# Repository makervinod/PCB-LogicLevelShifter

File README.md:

# PCB-LogicLevelShifter
## A 6-channel Logic Level Shifter PCB with on-board 3.3V Regulation

Components Required:
1. N-channel SMD(SOT-23) Mosfets x 6
2. 10k SMD(0805) Resistors x 12
3. LM11117-3.3 SMD(SOT-223) Voltage Regulator x 1
4. 0.1uF SMD(0805) Capacitors x 2
5. Red LED SMD(0805) x 1
6. 8-pin Male Headers 2.54mm Pitch x 2

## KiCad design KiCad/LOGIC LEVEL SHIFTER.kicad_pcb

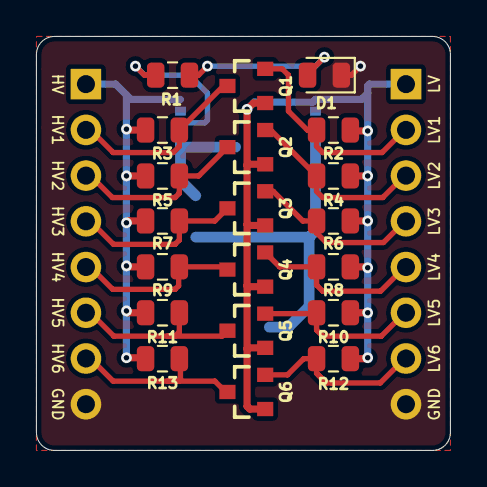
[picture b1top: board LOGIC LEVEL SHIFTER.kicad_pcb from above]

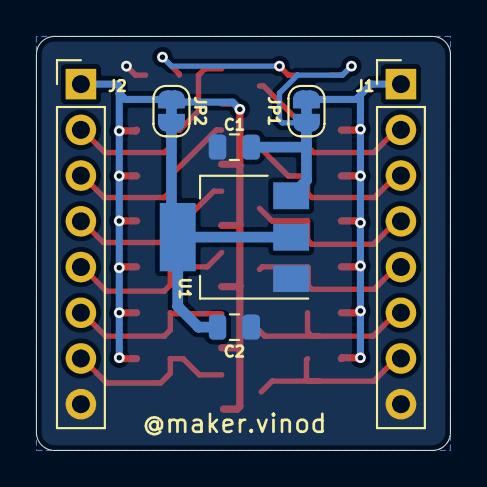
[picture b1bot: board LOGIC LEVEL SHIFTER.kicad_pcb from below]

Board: 2 copper layers, 23.0 x 23.0 mm, 27 parts (7 on the bottom side), 18 nets.

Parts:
C1, C2: 22uF; C_0805_2012Metric
D1: LED; LED_0805_2012Metric
J1: HV CONN; PinHeader_1x08_P2.54mm_Vertical
J2: LV CONN; PinHeader_1x08_P2.54mm_Vertical
JP1, JP2: Jumper_NC_Small; SolderJumper-2_P1.3mm_Bridged_RoundedPad1.0x1.5mm
Q1, Q2, Q3, Q4, Q5, Q6: AO3404A; SOT23-3
R1, R2, R3, R4, R5, R6, R7, R8, R9, R10, R11, R12, R13: 10k; R_0805_2012Metric
U1: AMS1117-3.3; SOT-223-3_TabPin2

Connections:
3V3: C2.1, JP2.1, U1.2
5V: C1.2, JP1.1, R1.2, U1.3
GND: C1.1, C2.2, D1.1, J1.8, J2.8, U1.1
HV: J1.1, JP1.2, R3.1, R5.1, R7.1, R9.1, R11.1, R13.1
HV_1: J1.2, Q1.3, R3.2
HV_2: J1.3, Q2.3, R5.2
HV_3: J1.4, Q3.3, R7.2
HV_4: J1.5, Q4.3, R9.2
HV_5: J1.6, Q5.3, R11.2
HV_6: J1.7, Q6.3, R13.2
LV: J2.1, JP2.2, Q1.1, Q2.1, Q3.1, Q4.1, Q5.1, Q6.1, R2.2, R4.2, R6.2, R8.2, R10.2, R12.2
LV_1: J2.2, Q1.2, R2.1
LV_2: J2.3, Q2.2, R4.1
LV_3: J2.4, Q3.2, R6.1
LV_4: J2.5, Q4.2, R8.1
LV_5: J2.6, Q5.2, R10.1
LV_6: J2.7, Q6.2, R12.1
unnamed: D1.2, R1.1

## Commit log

2021-04-25 Added Files
2021-04-25 Rename LICENSE to LICENSE.txt
2021-04-25 Create LICENSE
